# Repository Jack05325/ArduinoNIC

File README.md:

# ArduinoNIC - Rete a Bus Simile a ISO/OSI

Benvenuti nel progetto **ArduinoNIC**, una rete a bus progettata per simulare il funzionamento dello stack ISO/OSI fino al livello 3. L’obiettivo è creare un sistema in cui Arduino gestisce l’incapsulamento dei dati attraverso più livelli, aggiungendo header specifici a ciascun livello, e funge da **Network Interface Controller (NIC)** per dispositivi esterni.

___

## 🧰 Caratteristiche del progetto  
- **Rete a bus** gestita da Arduino tramite seriale.  
- **Incapsulamento dei dati** in più strati, seguendo i principi ISO/OSI.  
- Supporto per una **libreria Python** che comunica con Arduino per inviare e ricevere pacchetti.  
- Struttura **modulare**: ogni livello aggiunge il proprio header e controllo.  
- Ideale per chi vuole **imparare o sperimentare** con i protocolli di rete su hardware a basso costo.

___
## La struttura del pacchetto

|     | Dimensione (bit) | Descrizione |
| --- | --- | --- |
| **Livello Fisico** |     |     |
| Preamble | 16  | Sequenza di sincronizzazione (0xAA). |
| **Livello Data Link** |     |     |
| Indirizzo Dest. | 16  | Indirizzo fisico sul bus. |
| Indirizzo Mitt. | 16  |  |
| Tipo Protocollo | 8   | Protocollo superiore. |
| Checksum | 16  | Verifica integrità del livello 2. |
| **Livello Rete** |     |     |
| Indirizzo IP Dest. | 32  | Indirizzo logico del destinatario. |
| Indirizzo IP Mitt. | 32  | Indirizzo logico del mittente. |
| TTL | 8   | Tempo di vita. |
| Checksum | 16  | Verifica integrità livello 3. |
| **Livello Trasporto** |     |     |
| Porta Dest. | 16  | Porta logica del destinatario. |
| Porta Mitt. | 16  | Porta logica del mittente. |
| Seq. Number | 32  | Numero di sequenza. |
| Ack. Number | 32  | Numero di ack. |
| Flags | 8   | Controllo connessione. |
| Window Size | 16  | Dimensione della finestra. |
| Checksum | 16  | Verifica integrità livello 4. |
| **Livello Applicativo** |     |     |
| Dati | 128   | Contenuto effettivo del messaggio. |
___

## 📝 Nota Importante  

Non sono un esperto di networking o sistemi embedded, quindi il codice potrebbe non essere il più ottimizzato o robusto. Questo progetto è stato sviluppato per divertimento e per imparare.  

Se hai suggerimenti, miglioramenti o vuoi contribuire, sei il benvenuto! 😊  

___

## 📫 Contatti  

Per domande o suggerimenti, sentiti libero di aprire una **issue** o contattarmi direttamente!  

Grazie per il tuo interesse nel progetto! 💡

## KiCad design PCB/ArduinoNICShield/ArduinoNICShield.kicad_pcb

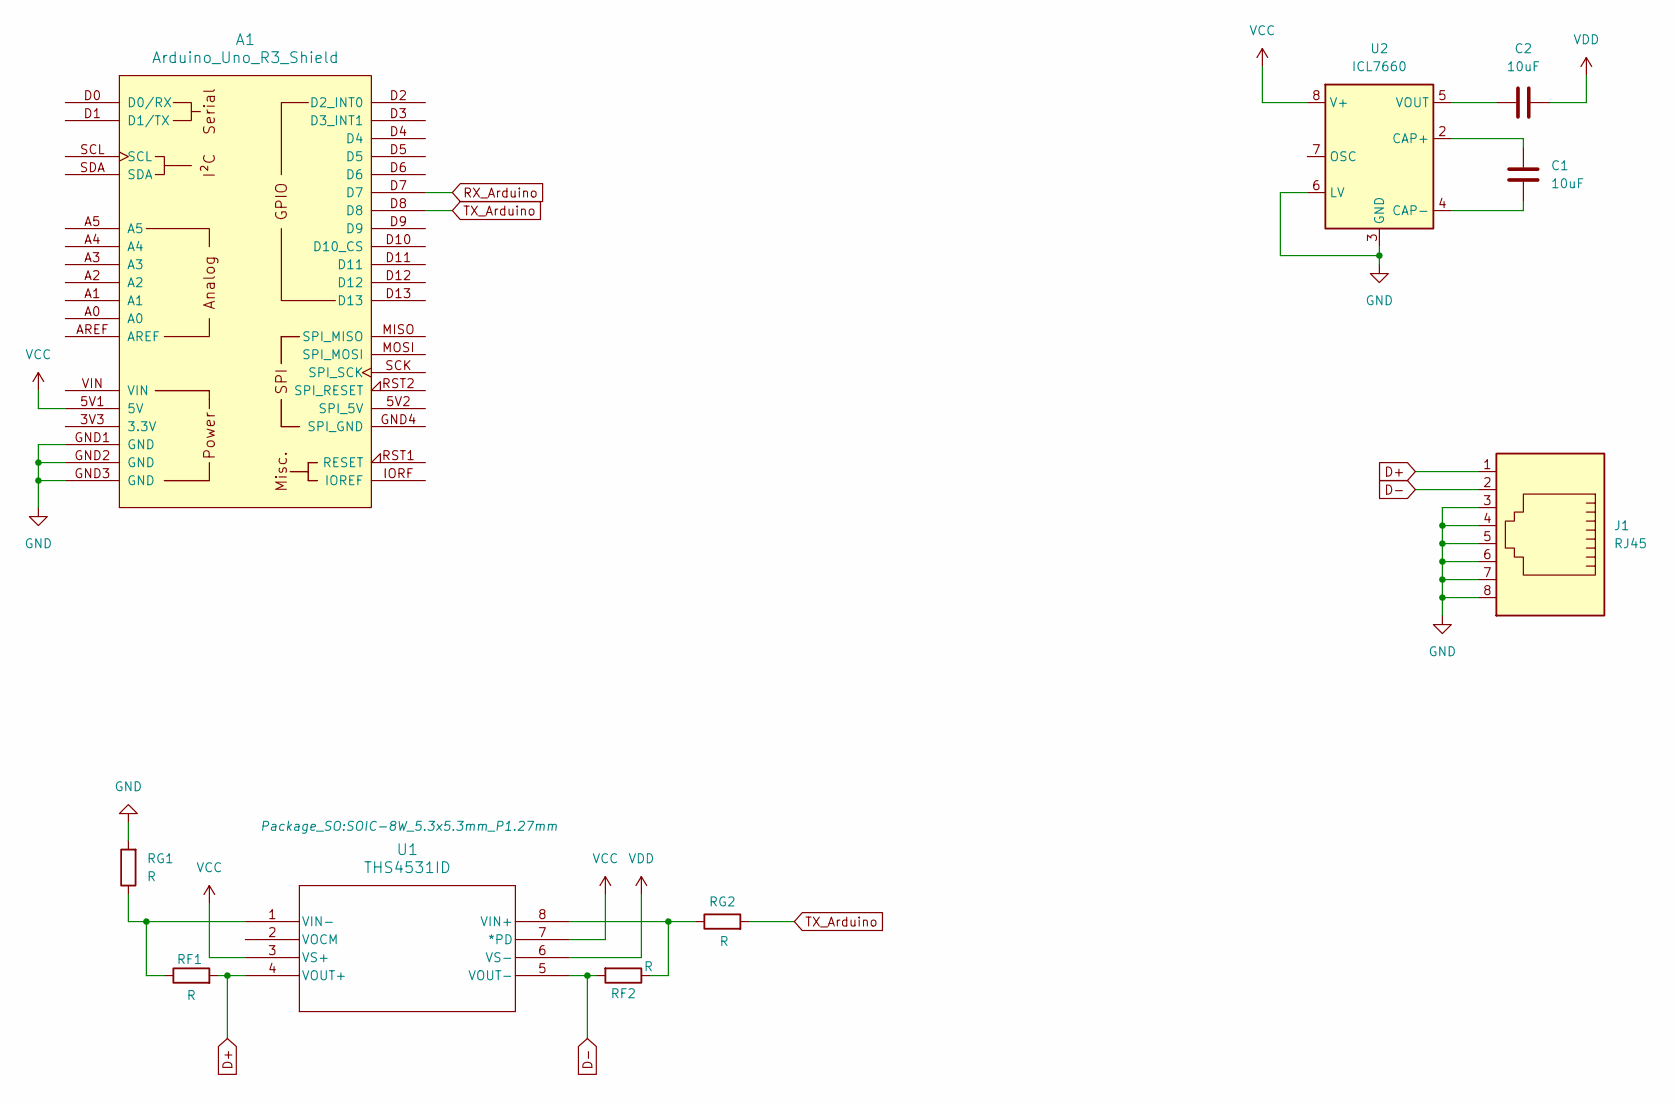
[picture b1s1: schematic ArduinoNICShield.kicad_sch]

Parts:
A1: Arduino_Uno_R3_Shield
C1, C2: 10uF; C_1206_3216Metric_Pad1.33x1.80mm_HandSolder
J1: RJ45; RJ45_Ninigi_GE
RF1, RF2: R; R_1206_3216Metric_Pad1.30x1.75mm_HandSolder
RG1, RG2: R; R_1206_3216Metric_Pad1.30x1.75mm_HandSolder
U1: THS4531ID; SOIC-8W_5.3x5.3mm_P1.27mm
U2: ICL7660; SOIC-8_5.23x5.23mm_P1.27mm

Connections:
D+: J1.1, RF1.2, U1.4 (VOUT+)
D-: J1.2, RF2.2, U1.5 (VOUT-)
GND: A1.GND1 (GND), A1.GND2 (GND), A1.GND3 (GND), J1.3, J1.4, J1.5, J1.6, J1.7, J1.8, RG1.2, U2.3 (GND), U2.6 (LV)
unnamed: RF2.1, RG2.1, U1.8 (VIN+)
unnamed: RF1.1, RG1.1, U1.1 (VIN-)
unnamed: C1.1, U2.2 (CAP+)
unnamed: C1.2, U2.4 (CAP-)
unnamed: C2.1, U2.5 (VOUT)
RX_Arduino: A1.D7
TX_Arduino: A1.D8, RG2.2
VCC: A1.5V1 (5V), U1.3 (VS+), U1.7 (*PD), U2.8 (V+)
VDD: C2.2, U1.6 (VS-)

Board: 2 copper layers, 10 parts (0 on the bottom side), 11 nets, no tracks yet.

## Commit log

2024-12-21 Aggiungi file di configurazione e documentazione per il progetto
2024-12-22 Creazione del progetto e libraria hamming implementata correttamente per la codifica di hamming
2024-12-22 implementa la libraria hamming.h sia per TX che RX con frame lungo 64bit mx
2024-12-22 implementata correttamente la libreria hamming.h
2024-12-23 tentavito implementazione hamming con array di byte non funzionante
2024-12-23 implementazione CRC in TX e RX
2024-12-26 Prima implementazione del layer 4 e primi test con la libreria python per la comumunicazione seriale
2025-01-01 Prima implementazione layer 3
2025-01-01 Prime implementazioni di layer 1 e 2, si sta implementando il sistema di trasmissiome dati sul bus
2025-01-01 Implementazione della trasmiosione seriale del pacchetto sul bus
2025-01-07 Implementazione della libreria SerialInputManager.h per la gestione dei dati da seriale e spacchettizazzione
2025-01-08 Correzione librerie layer1,layer2,layer3,layer4 con migliore utilizzo della memoria
2025-01-11 Implementazione protocollo UDP per l'invio di dati, ancora da testare
2025-01-11 bug fixing
2025-01-18 bug fixing e test di ricezione andati a buon fine
2025-03-11 Correction of the arduino library, and start of the implementation of the python interface
2025-03-13 implementation on the config menu from serial command for the python interface
